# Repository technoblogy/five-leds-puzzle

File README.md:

# Five LEDs Puzzle
A puzzle based on an ATtiny85 in which you have to press the buttons in the right sequence to light up all the LEDs.

For more information see: <http://www.technoblogy.com/show?3EL5>.

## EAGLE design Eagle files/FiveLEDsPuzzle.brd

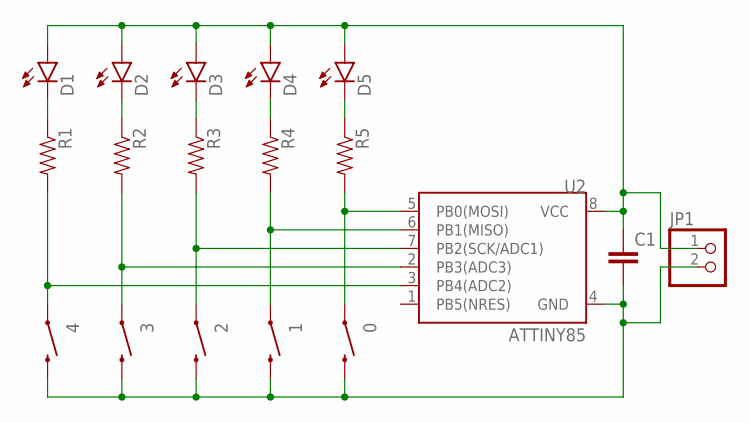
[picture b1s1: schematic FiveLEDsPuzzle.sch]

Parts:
0, 1, 2, 3, 4: SWITCH-MOMENTARY-2PTH; TACTILE-PTH
C1: 0.1UF-50V-20%(PTH)KIT-EZ; CAP-PTH-SMALL-KIT
D1, D2, D3, D4, D5: LED5MM
JP1: HEADER-1X2ROUND; 1X02_ROUND
R1, R2, R3, R4, R5: RESISTORAXIAL-0.3; AXIAL-0.3
U2: ATTINY85; DIP08

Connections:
unnamed: 3.1, R2.P$2 (2), U2.2 (PB3(ADC3))
unnamed: D2.K (C), R2.P$1 (1)
unnamed: 2.1, R3.P$2 (2), U2.7 (PB2(SCK/ADC1))
unnamed: D3.K (C), R3.P$1 (1)
unnamed: 4.1, R1.P$2 (2), U2.3 (PB4(ADC2))
unnamed: 1.1, R4.P$2 (2), U2.6 (PB1(MISO))
unnamed: D4.K (C), R4.P$1 (1)
unnamed: C1.1, D1.A, D2.A, D3.A, D4.A, D5.A, JP1.1, U2.8 (VCC)
unnamed: D5.K (C), R5.P$1 (1)
unnamed: 0.1, R5.P$2 (2), U2.5 (PB0(MOSI))
unnamed: 0.3 (2), 1.3 (2), 2.3 (2), 3.3 (2), 4.3 (2), C1.2, JP1.2, U2.4 (GND)
unnamed: D1.K (C), R1.P$1 (1)

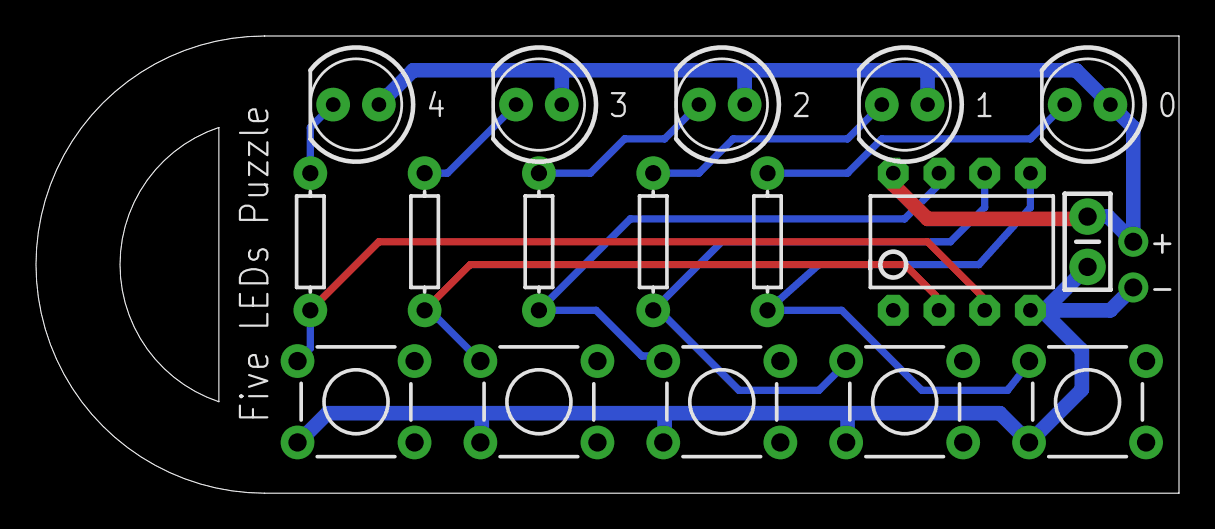
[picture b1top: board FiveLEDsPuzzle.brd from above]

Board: 2 copper layers, 63.5 x 25.4 mm, 18 parts (0 on the bottom side), 12 nets.

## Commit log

2021-01-04 Version 1 - 4th January 2021
2021-01-05 Version 3 - 5th January 2021
    Fixes #1: Correction to debounce when coming out of sleep.
2021-01-09 Pullups on to read switches.
2021-01-09 Version 4 - 9th January 2021
    Added code to turn on the pullup resistor when reading an input for more reliable operation as the battery voltage decreases.
2021-03-15 Version 5 - 15th March 2021

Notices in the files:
parts and their libraries:
SparkFun-LED: Licensing: Creative Commons ShareAlike 4.0 International - https://creativecommons.org/licenses/by-sa/4.0
microbuilder: This work is placed in the public domain, and may be freely used for commercial and non-commercial work with the following conditions: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
